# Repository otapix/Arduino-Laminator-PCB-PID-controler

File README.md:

# Arduino-Laminator-PCB-PID-controler
Laminator PCB - PID controler

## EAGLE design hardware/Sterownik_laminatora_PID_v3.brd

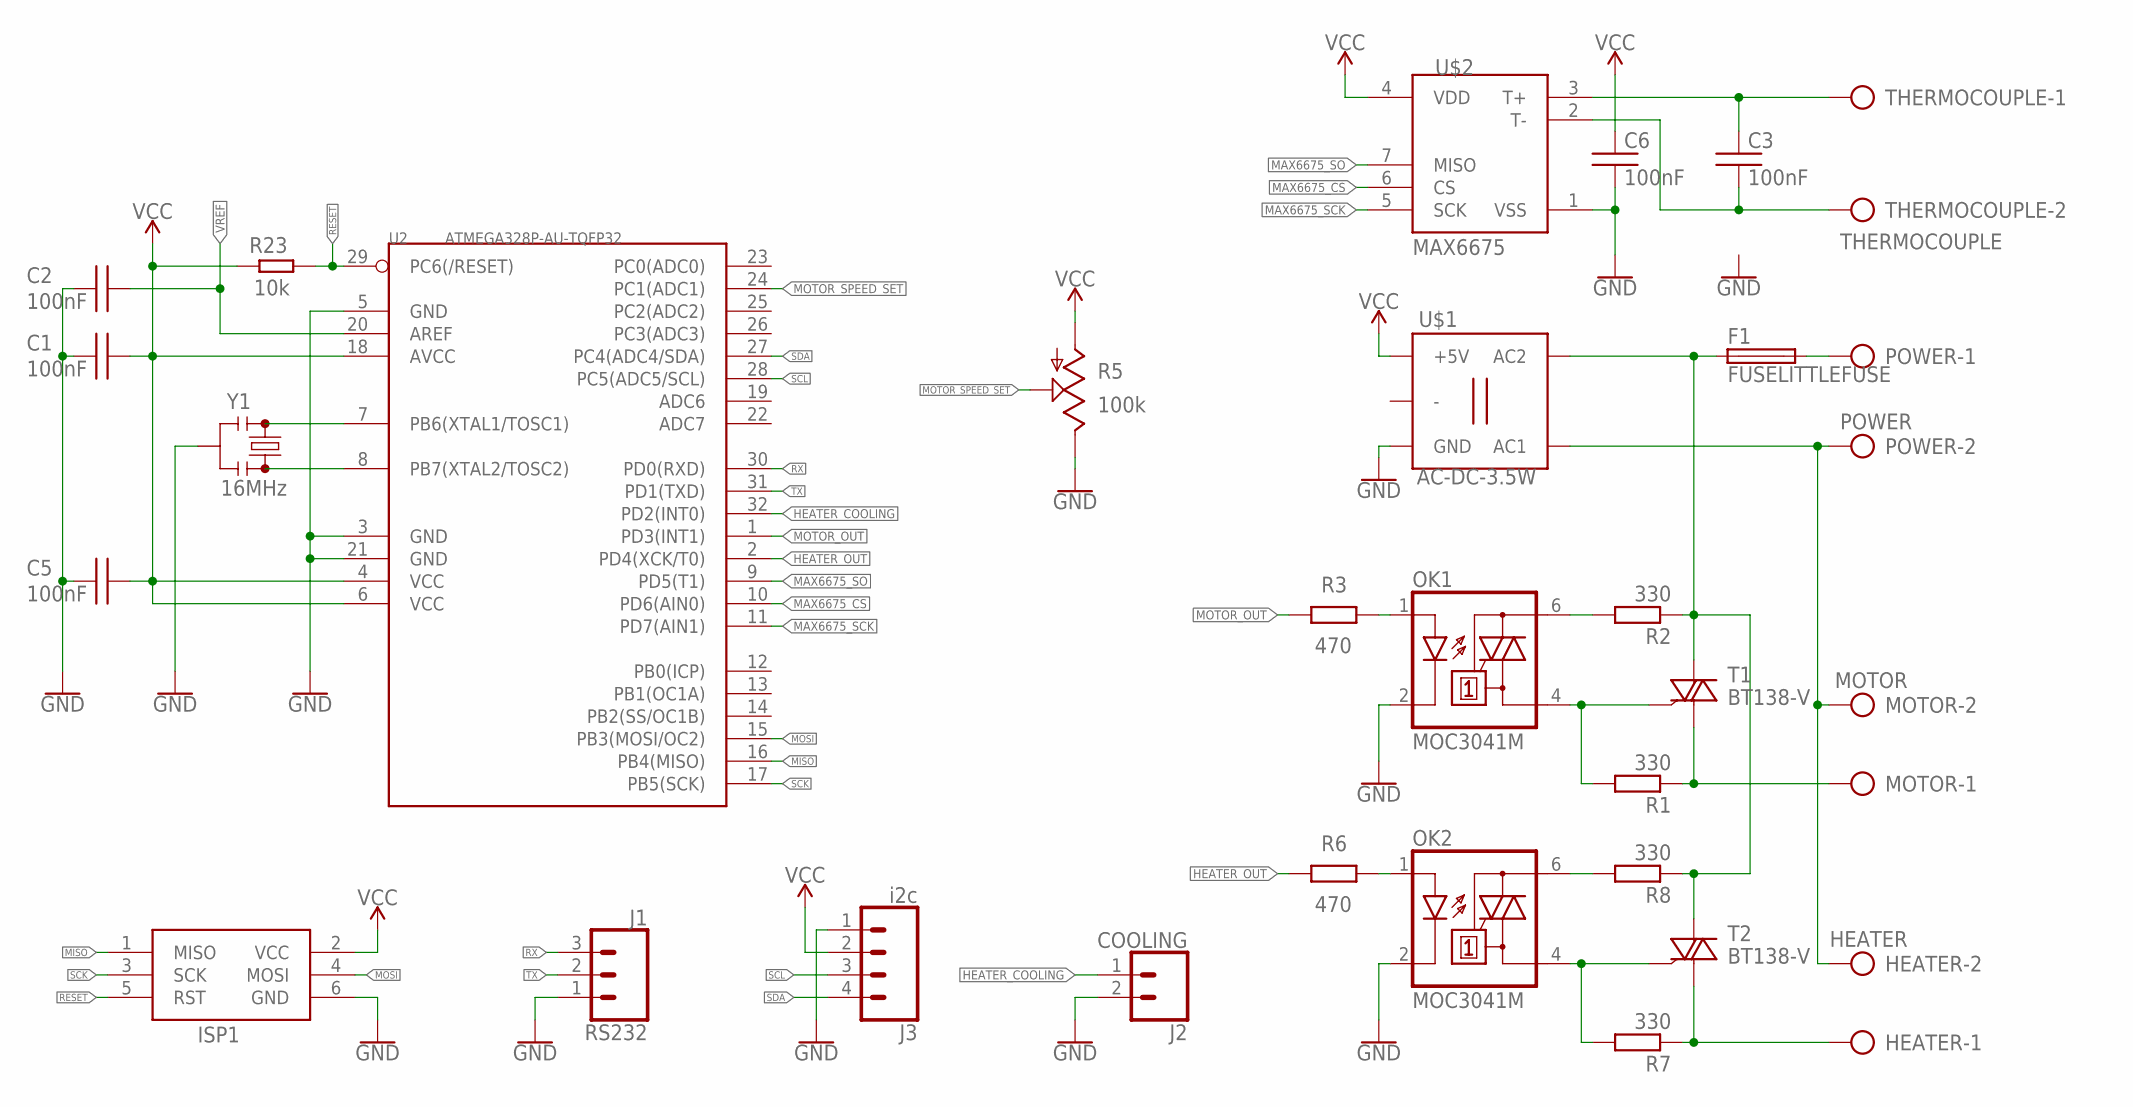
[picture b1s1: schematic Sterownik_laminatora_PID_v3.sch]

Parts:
C1, C2, C3, C5, C6: 100nF; C0805K
F1: FUSELITTLEFUSE; LITTLEFUSE
HEATER: HEATER; AK500/2
ISP1: AVRISP-6; AVRISP
J1: RS232; 1X03
J2: COOLING; 1X02
J3: i2c; 1X04
MOTOR: MOTOR; AK500/2
OK1, OK2: MOC3041M; DIL06
POWER: POWER; AK500/2
R1, R7: 330; M0805
R2, R8: 330; 0204/7
R3, R6: 470; M0805
R5: 100k; S63S
R23: 10k; M0805
T1, T2: BT138-V; TO220BV
THERMOCOUPLE: THERMOCOUPLE; AK500/2
U2: ATMEGA328P-AU-TQFP32; TQFP32-0.8-7X7MM
U$1: AC-DC-3.5W
U$2: MAX6675; SO08
Y1: 16MHz; RESONATOR-SMD-3.2X1.3

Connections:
GND: C1.2, C2.2, C5.1, C6.2, ISP1.6 (GND), J1.1, J2.2, J3.1, OK1.2 (C), OK2.2 (C), R5.E, U2.3 (GND), U2.5 (GND), U2.21 (GND), U$1.J2.1 (GND), U$2.1 (VSS), Y1.2
HEATER_COOLING: J2.1, U2.32 (PD2(INT0))
HEATER_OUT: R6.2, U2.2 (PD4(XCK/T0))
MAX6675_CS: U2.10 (PD6(AIN0)), U$2.6 (CS)
MAX6675_SCK: U2.11 (PD7(AIN1)), U$2.5 (SCK)
MAX6675_SO: U2.9 (PD5(T1)), U$2.7 (MISO)
MISO: ISP1.1 (MISO), U2.16 (PB4(MISO))
MOSI: ISP1.4 (MOSI), U2.15 (PB3(MOSI/OC2))
MOTOR_OUT: R3.2, U2.1 (PD3(INT1))
MOTOR_SPEED_SET: R5.S, U2.24 (PC1(ADC1))
unnamed: C3.1, THERMOCOUPLE.1, U$2.3 (T+)
unnamed: OK2.1 (A), R6.1
unnamed: HEATER.2, MOTOR.2, POWER.2, U$1.J1.1 (AC1)
unnamed: OK1.1 (A), R3.1
unnamed: MOTOR.1, R1.1, T1.T1 (A1)
unnamed: OK2.4 (A1), R7.2, T2.G
unnamed: OK1.4 (A1), R1.2, T1.G
unnamed: OK2.6 (A2), R8.2
unnamed: C3.2, THERMOCOUPLE.2, U$2.2 (T-)
unnamed: F1.1, R2.1, R8.1, T1.T2 (A2), T2.T2 (A2), U$1.J1.2 (AC2)
unnamed: OK1.6 (A2), R2.2
unnamed: HEATER.1, R7.1, T2.T1 (A1)
unnamed: U2.7 (PB6(XTAL1/TOSC1)), Y1.1
unnamed: U2.8 (PB7(XTAL2/TOSC2)), Y1.3
unnamed: F1.2, POWER.1
RESET: ISP1.5 (RST), R23.2, U2.29 (PC6(/RESET))
RX: J1.3, U2.30 (PD0(RXD))
SCK: ISP1.3 (SCK), U2.17 (PB5(SCK))
SCL: J3.3, U2.28 (PC5(ADC5/SCL))
SDA: J3.4, U2.27 (PC4(ADC4/SDA))
TX: J1.2, U2.31 (PD1(TXD))
VCC: C1.1, C5.2, C6.1, ISP1.2 (VCC), J3.2, R5.A, R23.1, U2.4 (VCC), U2.6 (VCC), U2.18 (AVCC), U$1.J2.3 (+5V), U$2.4 (VDD)
VREF: C2.1, U2.20 (AREF)

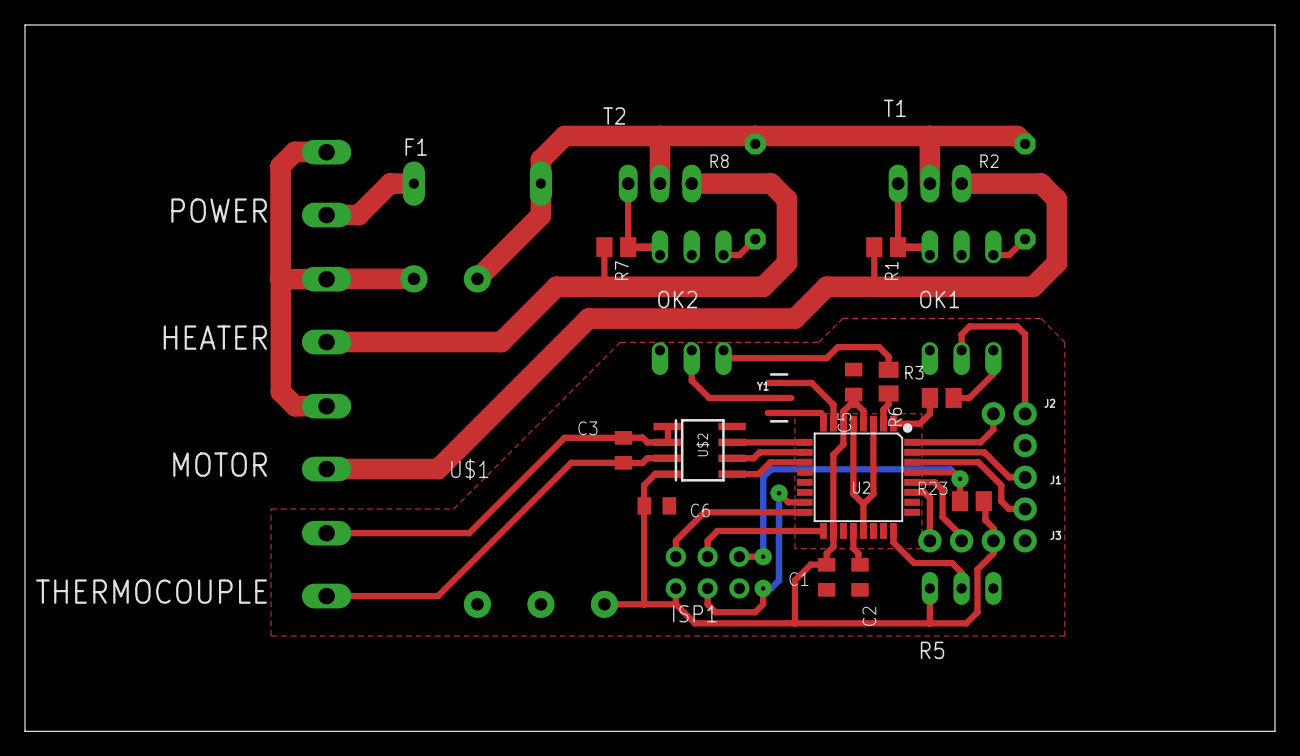
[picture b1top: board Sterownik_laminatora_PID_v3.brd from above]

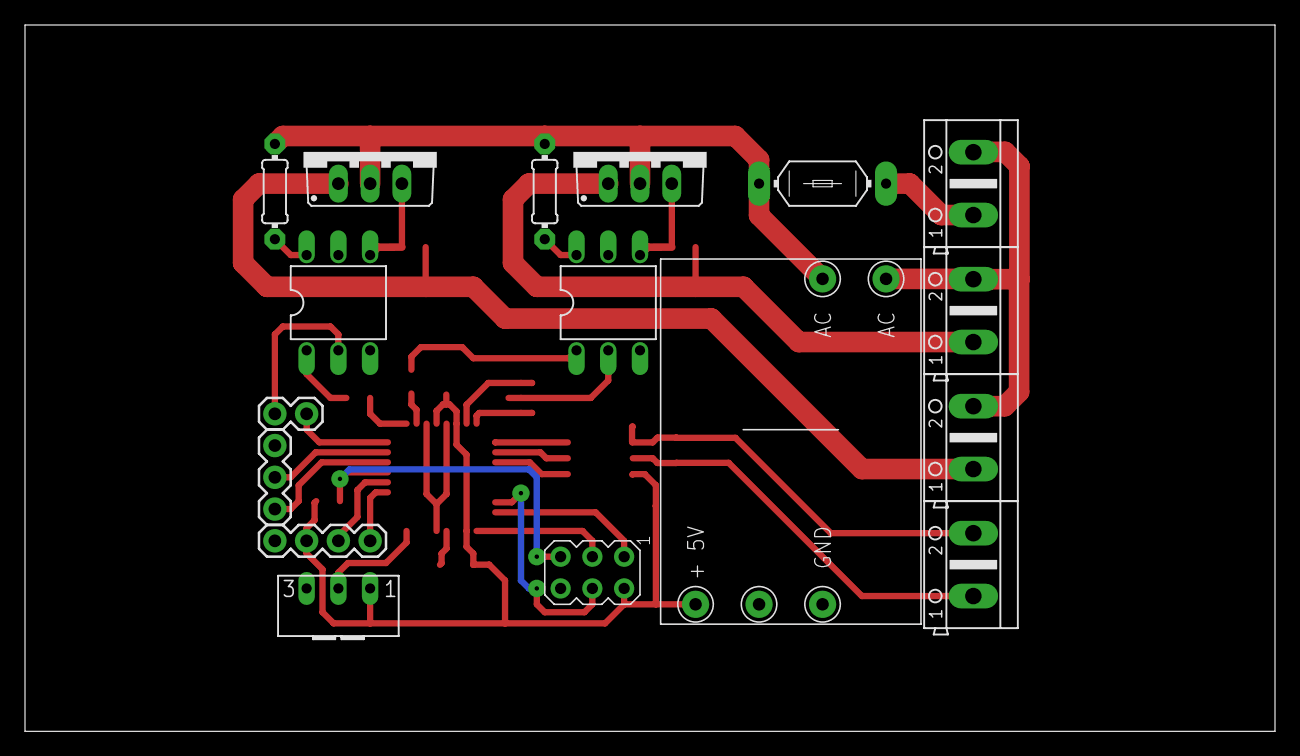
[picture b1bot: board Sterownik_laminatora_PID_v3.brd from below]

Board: 2 copper layers, 100.0 x 56.5 mm, 30 parts (17 on the bottom side), 33 nets.

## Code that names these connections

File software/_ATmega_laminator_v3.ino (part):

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#define use_cooling_switch_button   1 // 1 - jezeli chcesz uzywac przelacznika do wlaczenie chlodzenia,
                                      // 0 - jezeli chcesz uzyc przycisku do wlaczenie chlodzenia

#define MAX6675_SO                  5  //  9 // PD5
#define MAX6675_CS                  6  // 10 // PD6
#define MAX6675_SCK                 7  // 11 // PD7

#define MOTOR_PIN                   3  //  1 // PD3
#define MOTOR_SPEED_SET_PIN         A1 // 24 // PC1

#define MOTOR_TIME_ON               200      // ms > 0
#define MOTOR_TIME_OFF_MIN          100      // ms > 0
#define MOTOR_TIME_OFF_MAX          8000     // ms > 0

#define HEATER_PIN                  4  //  2 // PD4
#define HEATER_COOLING_PIN          2  // 32 // PD2

#define HEATER_TEMP                 170      // *C
#define HEATER_TEMP_MIN             20       // *C
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    #include <EEPROM.h>
    #include <TM1637Display.h>
    #define DISPLAY_BRIGHTNES       2  // 0 - 7
    #define DISPLAY_CLK             A4 // 27 // PC4   // Set the CLK pin connection to the display
    #define DISPLAY_DIO             A5 // 26 // PC5   // Set the DIO pin connection to the display
    TM1637Display display(DISPLAY_CLK, DISPLAY_DIO);
#endif

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    static uint32_t update_temp_time;
    if(millis() - update_temp_time >= 200) {
        update_temp_time = millis();
        pinMode(MAX6675_CS, OUTPUT);
        pinMode(MAX6675_SO, INPUT);
        pinMode(MAX6675_SCK, OUTPUT);
        digitalWrite(MAX6675_CS, LOW);
        _delay_ms(1);
        v = shiftIn(MAX6675_SO, MAX6675_SCK, MSBFIRST);
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
    void setupHeatingTemp(void) {
        EEPROM.get(0, heater_temp);
        if(digitalRead(HEATER_COOLING_PIN)) {
            uint8_t s[] = { 0b01110100, 0b00000000 };
            uint8_t state[] = {s[0]};
            display.showNumberDec(heater_temp, false);
            display.setSegments(state, 1, 0);
            uint32_t update_heating_temp = millis();
            int16_t t1 = analogRead(MOTOR_SPEED_SET_PIN);
            while(millis() - update_heating_temp < 5000) {
                int16_t t2 = analogRead(MOTOR_SPEED_SET_PIN);
                if((t2 > t1 + 100) || (t2 < t1 - 100)) {
                    bool x = 1;
                    while(millis() - update_heating_temp < 15000) {
                        heater_temp = analogRead(MOTOR_SPEED_SET_PIN);
                        heater_temp = map(heater_temp, 0, 1023, HEATER_TEMP_MIN, HEATER_TEMP_MAX);
                        x = !x;
                        state[0] = s[x];
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
    pinMode(MOTOR_PIN, OUTPUT);
    pinMode(HEATER_PIN, OUTPUT);
    pinMode(HEATER_COOLING_PIN, INPUT_PULLUP);

    digitalWrite(MOTOR_PIN, motor_state);
    digitalWrite(HEATER_PIN, heater_state);
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    Input = readMAX6675();

    #if use_cooling_switch_button
        heater_cooling_state = !digitalRead(HEATER_COOLING_PIN);
    #else
        if(!digitalRead(HEATER_COOLING_PIN)) {
            heater_cooling_state = !heater_cooling_state;
            while(!digitalRead(HEATER_COOLING_PIN)) {
                _delay_ms(50);
            }
        }
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        digitalWrite(MOTOR_PIN, HIGH);
    } else {
        // motor ///////////////////////////////////////////////////////////
        motor_time_off = analogRead(MOTOR_SPEED_SET_PIN);
        motor_time_off = map(motor_time_off, 0, 1023, 0, MOTOR_TIME_OFF_MAX);

        if(motor_state) {
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

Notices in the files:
parts and their libraries:
SparkFun-Connectors: Licensing: Creative Commons ShareAlike 4.0 International - https://creativecommons.org/licenses/by-sa/4.0
diy-modules: Released under the Creative Commons Attribution 4.0 International License: http://creativecommons.org/licenses/by/4.0
